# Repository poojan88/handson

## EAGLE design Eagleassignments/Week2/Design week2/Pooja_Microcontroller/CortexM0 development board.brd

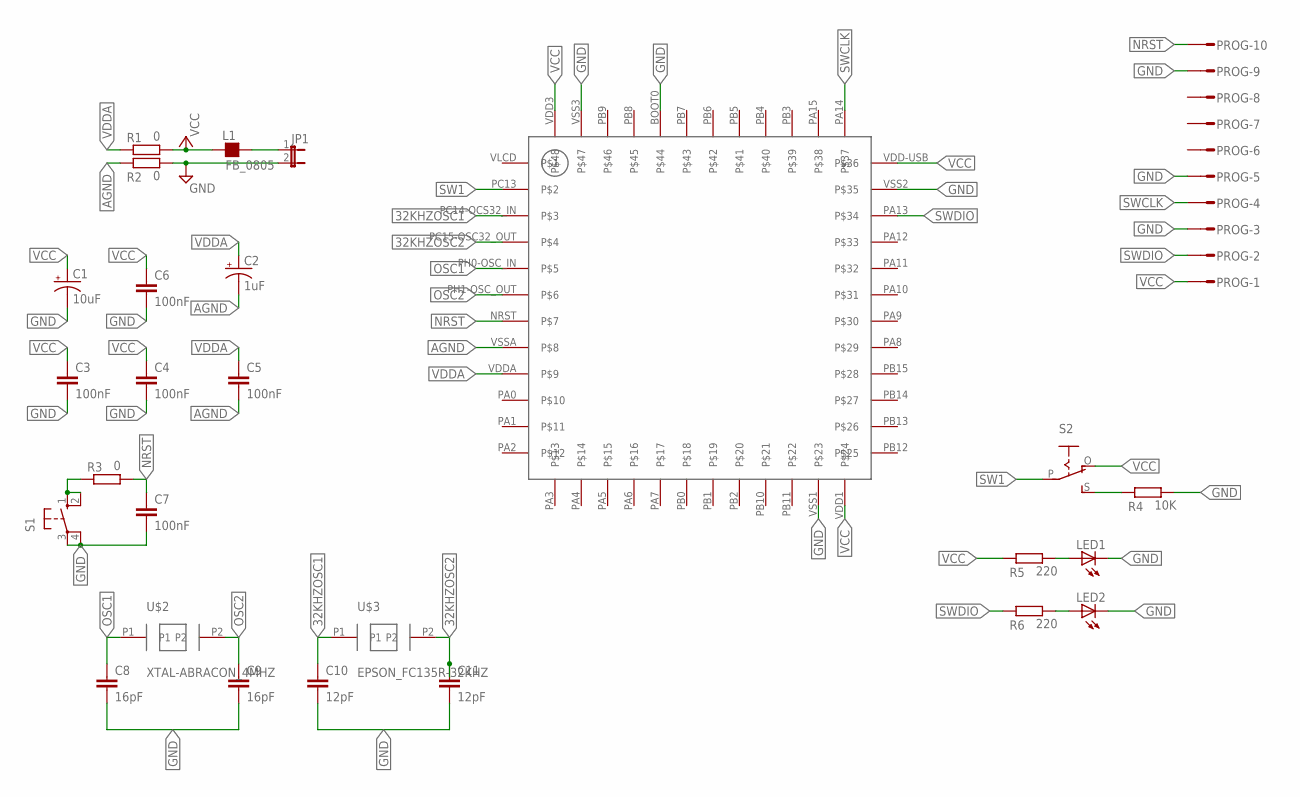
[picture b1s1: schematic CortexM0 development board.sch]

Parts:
C1: 10uF; CAPMP3216X180N
C2: 1uF; CAPMP3216X180N
C3, C4, C5, C6, C7: 100nF; C0805
C8, C9: 16pF; C0805
C10, C11: 12pF; C0805
JP1: JP1E; JP1
L1: FB_0805; L0805
LED1, LED2: LED; SMARTLED-TTW
PROG: S10P
R1, R2, R3: 0; R0805
R4: 10K; R0805
R5, R6: 220; R0805
S1: 10-XX; B3F-10XX
S2: EG1218S; EG1218
U$1: LQFP_48; STM32L083CZ
U$2: XTAL-ABRACON_4MHZ; XTAL_ABRACON_4MHZ
U$3: EPSON_FC135R-32KHZ; EPSON_FC135R_32KHZ

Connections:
32KHZOSC1: C10.1, U$1.PC14-OCS32_IN, U$3.P1
32KHZOSC2: C11.1, U$1.PC15-OSC32_OUT, U$3.P2
AGND: C2.2 (-), C5.2, R2.1, U$1.VSSA
GND: C1.2 (-), C3.2, C4.2, C6.2, C7.2, C8.2, C9.2, C10.2, C11.2, JP1.2, LED1.C@1 (C), LED2.C@1 (C), PROG.3, PROG.5, PROG.9, R2.2, R4.2, S1.3, S1.4 (P1), U$1.BOOT0, U$1.VSS1, U$1.VSS2, U$1.VSS3
unnamed: JP1.1, L1.2
unnamed: LED1.A@1 (A), R5.2
unnamed: R4.1, S2.S
unnamed: R3.1, S1.1 (S), S1.2 (S1)
unnamed: LED2.A@1 (A), R6.2
NRST: C7.1, PROG.10, R3.2, U$1.NRST
OSC1: C8.1, U$1.PH0-OSC_IN, U$2.P1
OSC2: C9.1, U$1.PH1-OSC_OUT, U$2.P2
SW1: S2.P, U$1.PC13
SWCLK: PROG.4, U$1.PA14
SWDIO: PROG.2, R6.1, U$1.PA13
VCC: C1.1 (+), C3.1, C4.1, C6.1, L1.1, PROG.1, R1.2, R5.1, S2.O, U$1.VDD1, U$1.VDD3, U$1.VDD-USB
VDDA: C2.1 (+), C5.1, R1.1, U$1.VDDA

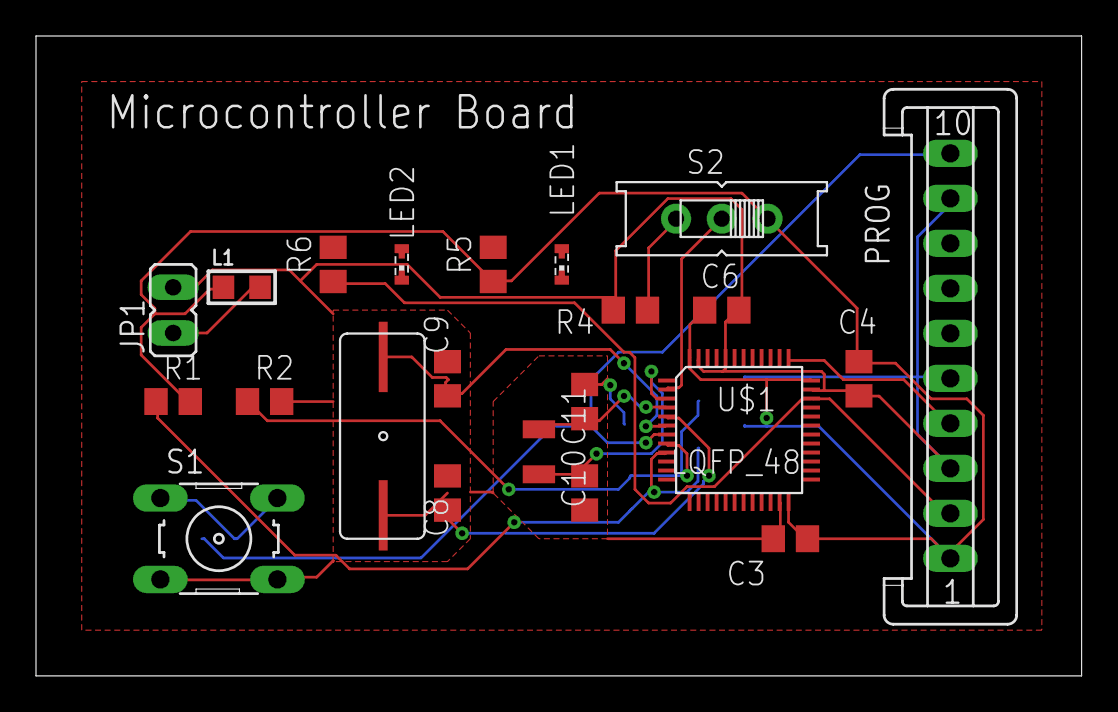
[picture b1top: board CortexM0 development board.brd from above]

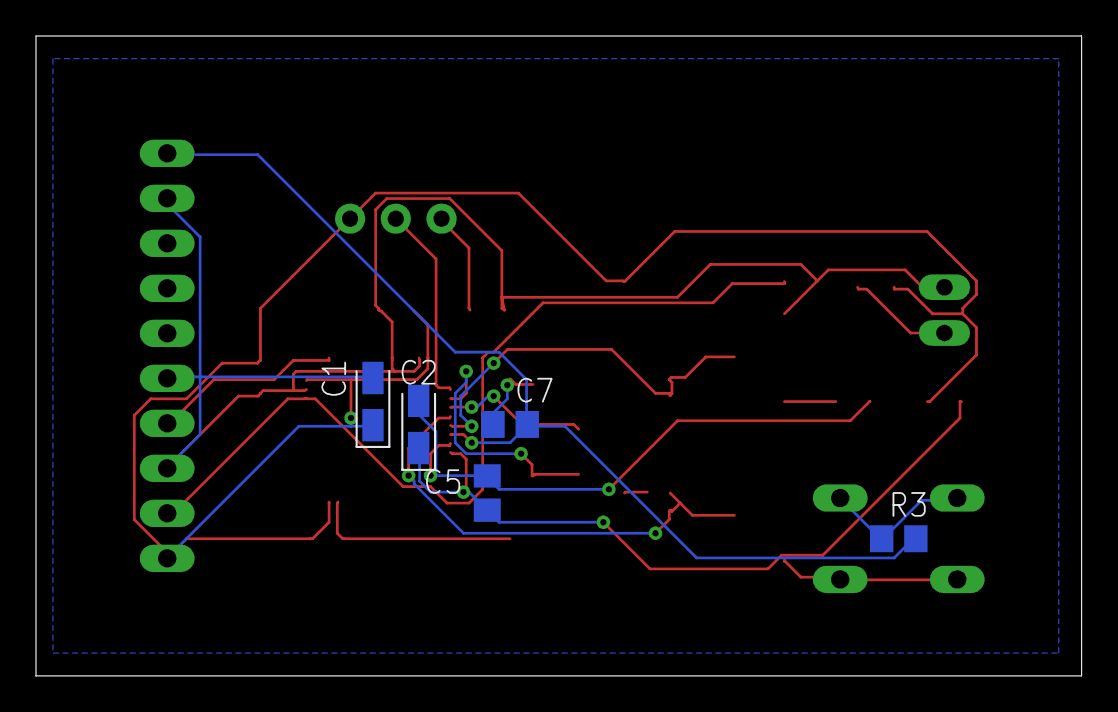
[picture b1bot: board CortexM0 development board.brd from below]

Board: 2 copper layers, 58.1 x 35.5 mm, 27 parts (5 on the bottom side), 17 nets.

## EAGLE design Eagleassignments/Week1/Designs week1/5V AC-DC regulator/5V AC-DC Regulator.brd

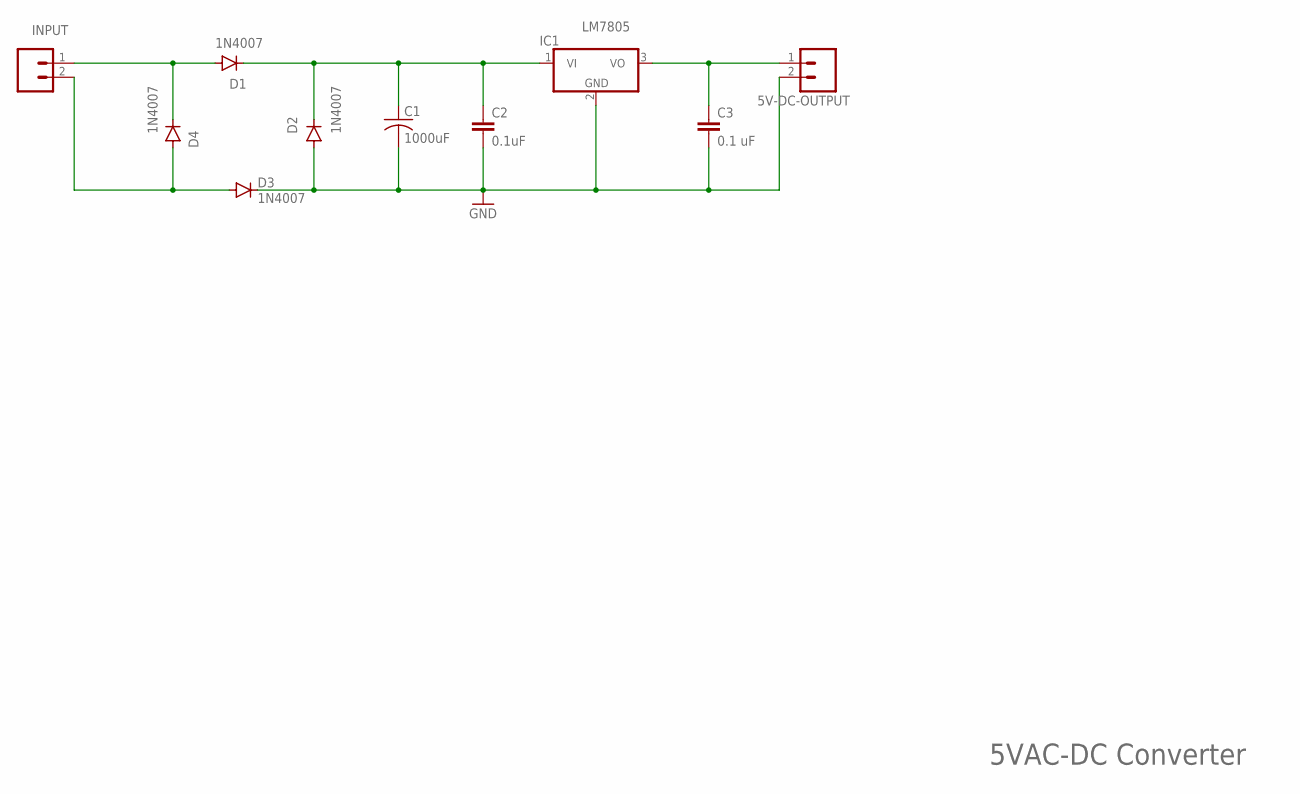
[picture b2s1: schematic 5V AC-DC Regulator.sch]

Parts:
5V-DC-OUTPUT: M02; 02P
C1: 1000uF; C025-024X044
C2: 0.1uF; C025-025X050
C3: 0.1 uF; C025-025X050
D1, D2, D3, D4: 1N4007; DO41-10
IC1: LM7805; TO220V
INPUT: M02; 02P

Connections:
GND: 5V-DC-OUTPUT.2, C1.2, C2.2, C3.2, D2.A, D3.C, IC1.2 (GND)
unnamed: D1.A, D4.C, INPUT.1
unnamed: C1.1, C2.1, D1.C, D2.C, IC1.1 (VI)
unnamed: D3.A, D4.A, INPUT.2
unnamed: 5V-DC-OUTPUT.1, C3.1, IC1.3 (VO)

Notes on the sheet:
5VAC-DC Converter

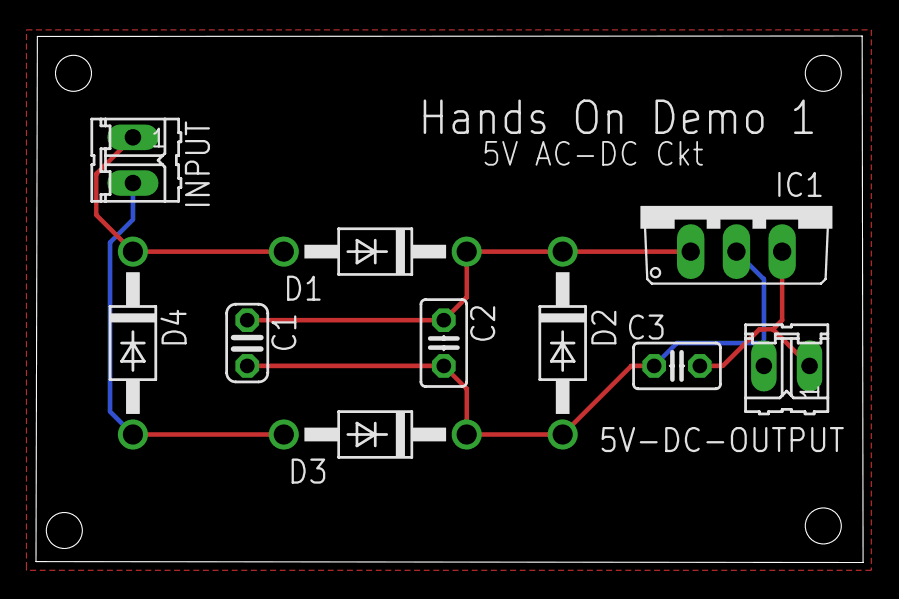
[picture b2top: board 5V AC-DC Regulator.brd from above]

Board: 2 copper layers, 45.9 x 29.3 mm, 10 parts (0 on the bottom side), 5 nets.

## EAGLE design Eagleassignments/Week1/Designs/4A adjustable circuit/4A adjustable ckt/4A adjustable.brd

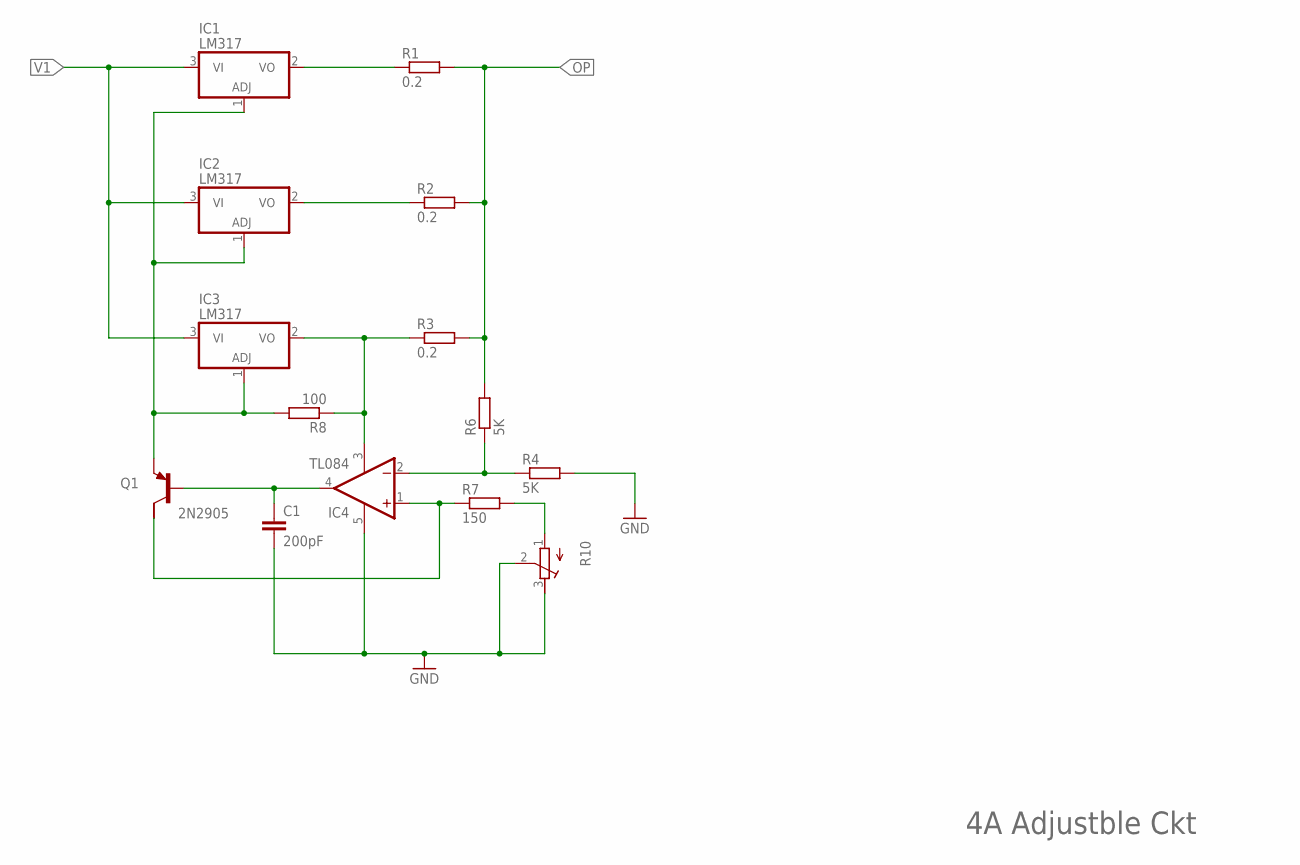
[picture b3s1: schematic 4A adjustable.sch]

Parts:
C1: 200pF; C025-025X050
IC1, IC2, IC3: LM317; TO92
IC4: TL084; CB360
Q1: 2N2905; SOT89
R1, R2, R3: 0.2; 0207/10
R4, R6: 5K; 0207/10
R7: 150; 0207/10
R8: 100; 0207/10
R10: R-TRIMM3339P; RTRIM3339P

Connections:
GND: C1.2, IC4.5 (V+), R4.2, R10.2 (S), R10.3 (E)
unnamed: IC3.2 (VO), IC4.3 (GND), R3.1, R8.1
unnamed: IC1.1 (ADJ), IC2.1 (ADJ), IC3.1 (ADJ), Q1.3 (E), R8.2
unnamed: IC4.2 (-IN), R4.1, R6.1
unnamed: IC1.2 (VO), R1.1
unnamed: IC2.2 (VO), R2.1
unnamed: IC4.1 (+IN), Q1.2 (C), R7.1
unnamed: C1.1, IC4.4 (OUT), Q1.1 (B)
unnamed: R7.2, R10.1 (A)
OP: R1.2, R2.2, R3.2, R6.2
V1: IC1.3 (VI), IC2.3 (VI), IC3.3 (VI)

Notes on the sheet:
4A Adjustble Ckt

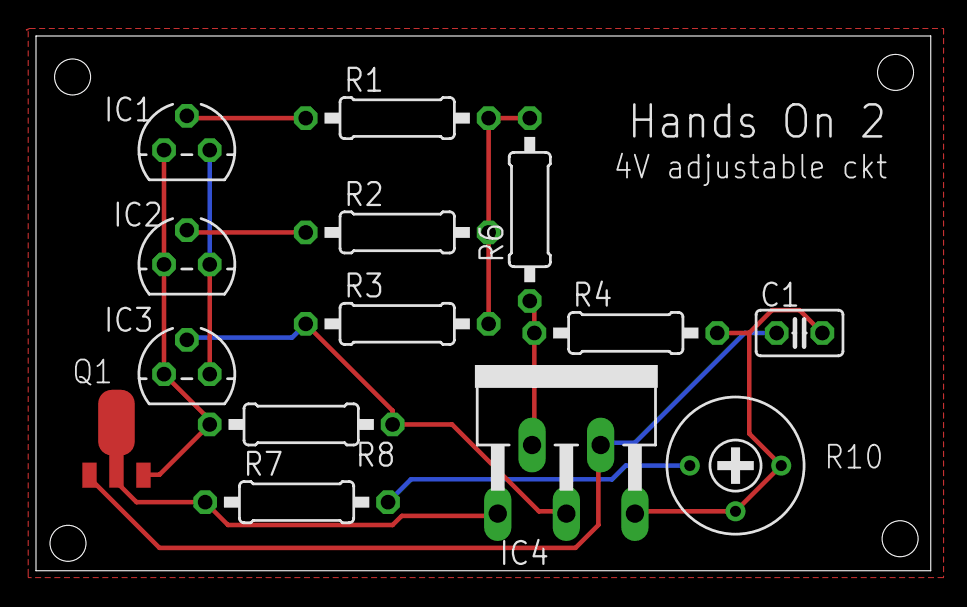
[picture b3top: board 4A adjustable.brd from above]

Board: 2 copper layers, 49.7 x 29.7 mm, 14 parts (0 on the bottom side), 11 nets.

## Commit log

2021-02-20 added git ignore file
2021-02-20 added readme.md
2021-02-20 added week1 assignments
2021-03-06 added microcontroller files to the repository

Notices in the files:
parts and their libraries:
rc-master-smd: Copyright (C) 2007, Bob Starr
